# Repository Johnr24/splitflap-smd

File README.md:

# splitflap-smd
modifications of scottbez's sensor PCB design to work and fit within david kingsmans design,

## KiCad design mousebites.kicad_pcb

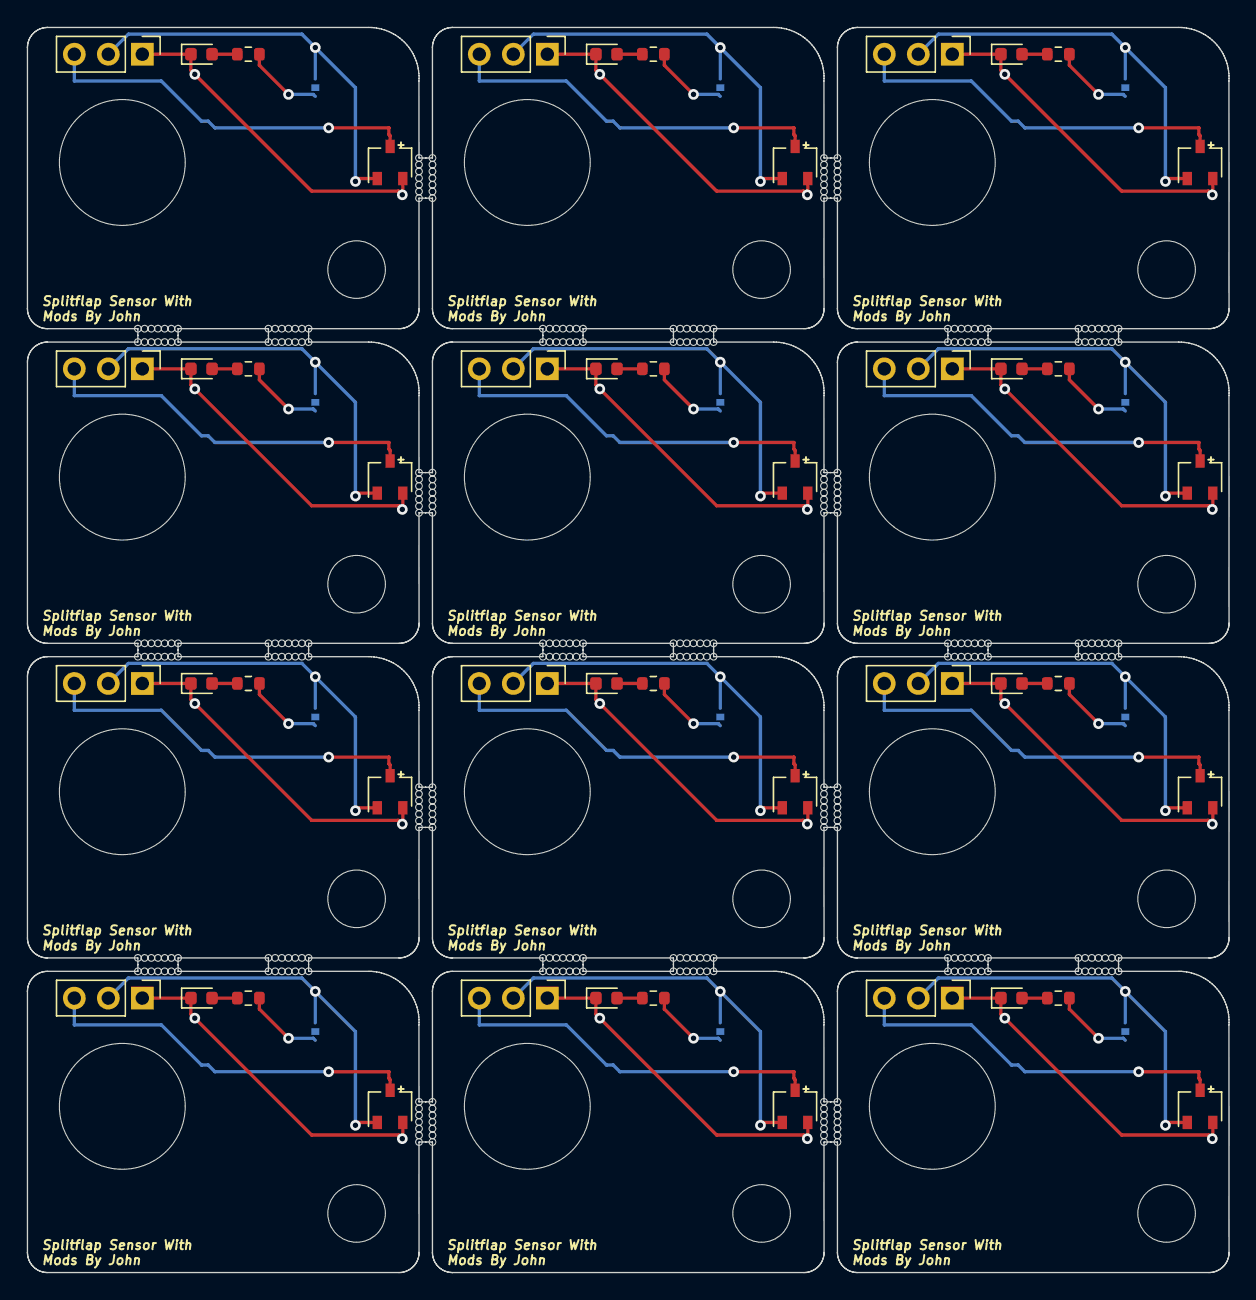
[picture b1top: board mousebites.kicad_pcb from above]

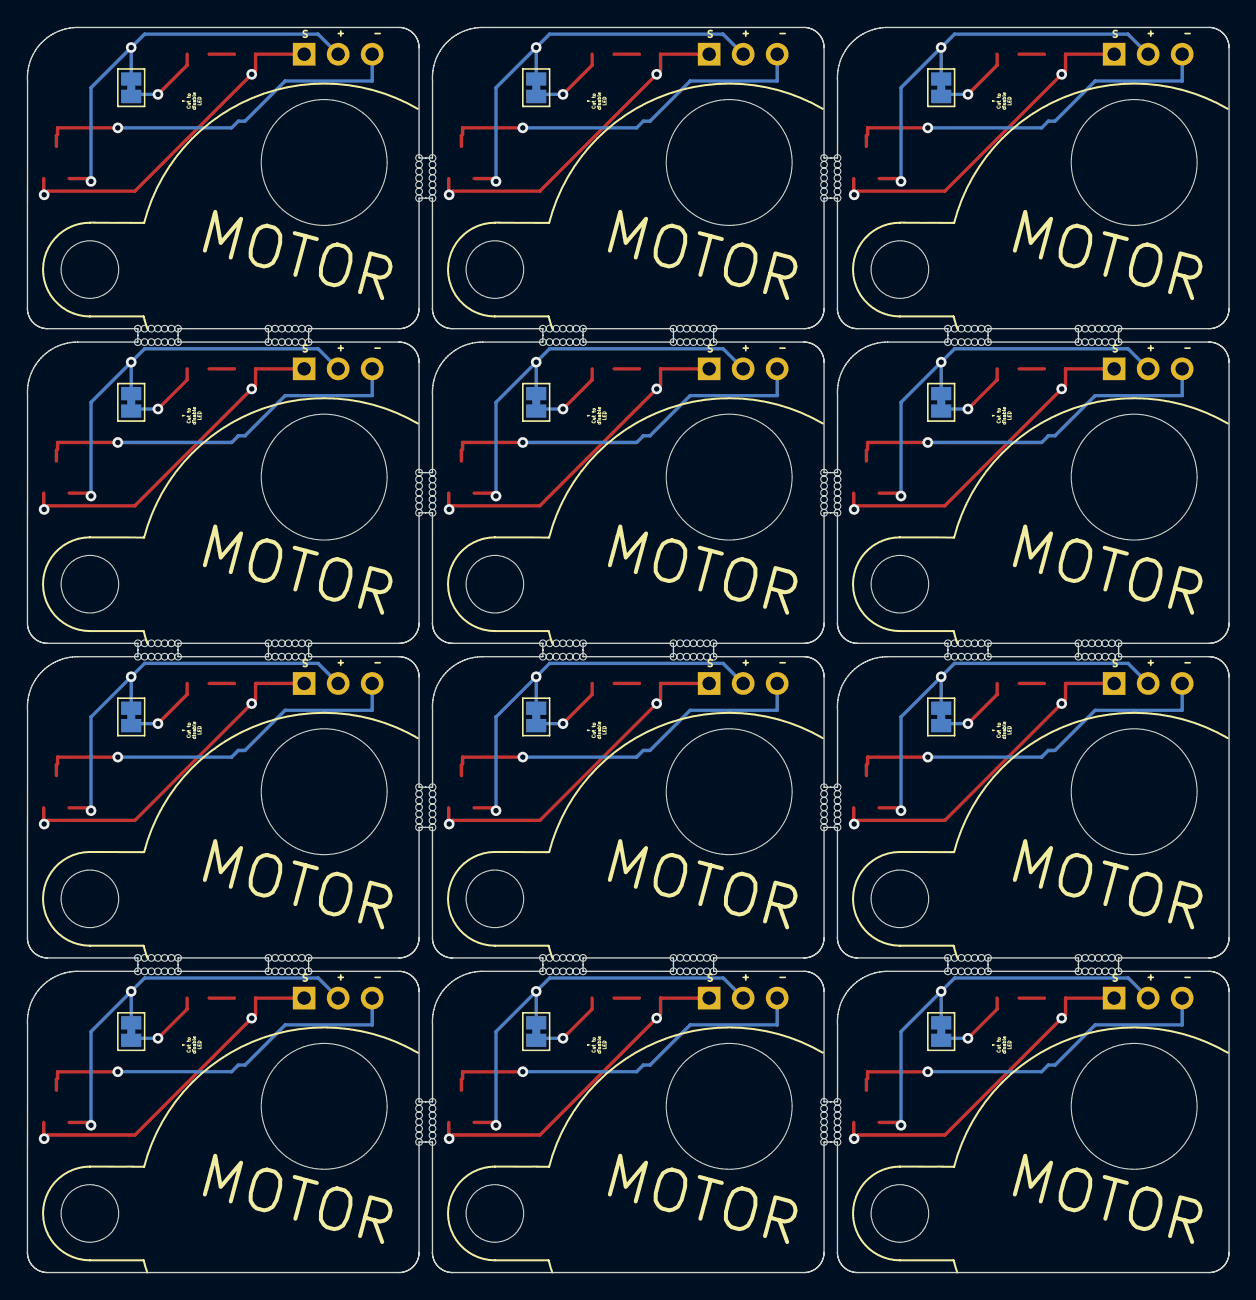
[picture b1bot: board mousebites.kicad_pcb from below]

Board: 2 copper layers, 89.8 x 93.0 mm, 448 parts (12 on the bottom side), 60 nets.

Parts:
D1, D1#2, D1#3, D1#4, D1#5, D1#6, D1#7, D1#8, D1#9, D1#10, D1#11, D1#12: LED RED; LED_0603_1608Metric
H1, H1#2, H1#3, H1#4, H1#5, H1#6, H1#7, H1#8, H1#9, H1#10, H1#11, H1#12: MountingHole; MountingHole_4.3mm_M4_ISO7380
H2, H2#2, H2#3, H2#4, H2#5, H2#6, H2#7, H2#8, H2#9, H2#10, H2#11, H2#12: MountingHole; hole_9.4
J1, J1#2, J1#3, J1#4, J1#5, J1#6, J1#7, J1#8, J1#9, J1#10, J1#11, J1#12: HEADER MALE RA; PinHeader_1x03_P2.54mm_Vertical
JP1, JP1#2, JP1#3, JP1#4, JP1#5, JP1#6, JP1#7, JP1#8, JP1#9, JP1#10, JP1#11, JP1#12: LED enable; SolderJumper-2_P1.3mm_Bridged_Pad1.0x1.5mm
KiKit_MB_1_1, KiKit_MB_1_2, KiKit_MB_1_3, KiKit_MB_1_4, KiKit_MB_1_5, KiKit_MB_1_6, KiKit_MB_1_7, KiKit_MB_2_1, KiKit_MB_2_2, KiKit_MB_2_3, KiKit_MB_2_4, KiKit_MB_2_5, KiKit_MB_2_6, KiKit_MB_2_7, KiKit_MB_3_1, KiKit_MB_3_2, KiKit_MB_3_3, KiKit_MB_3_4, KiKit_MB_3_5, KiKit_MB_3_6, KiKit_MB_3_7, KiKit_MB_4_1, KiKit_MB_4_2, KiKit_MB_4_3, KiKit_MB_4_4, KiKit_MB_4_5, KiKit_MB_4_6, KiKit_MB_4_7, KiKit_MB_5_1, KiKit_MB_5_2, KiKit_MB_5_3, KiKit_MB_5_4, KiKit_MB_5_5, KiKit_MB_5_6, KiKit_MB_5_7, KiKit_MB_6_1, KiKit_MB_6_2, KiKit_MB_6_3, KiKit_MB_6_4, KiKit_MB_6_5, KiKit_MB_6_6, KiKit_MB_6_7, KiKit_MB_7_1, KiKit_MB_7_2, KiKit_MB_7_3, KiKit_MB_7_4, KiKit_MB_7_5, KiKit_MB_7_6, KiKit_MB_7_7, KiKit_MB_8_1, KiKit_MB_8_2, KiKit_MB_8_3, KiKit_MB_8_4, KiKit_MB_8_5, KiKit_MB_8_6, KiKit_MB_8_7, KiKit_MB_9_1, KiKit_MB_9_2, KiKit_MB_9_3, KiKit_MB_9_4, KiKit_MB_9_5, KiKit_MB_9_6, KiKit_MB_9_7, KiKit_MB_10_1, KiKit_MB_10_2, KiKit_MB_10_3, KiKit_MB_10_4, KiKit_MB_10_5, KiKit_MB_10_6, KiKit_MB_10_7, KiKit_MB_11_1, KiKit_MB_11_2, KiKit_MB_11_3, KiKit_MB_11_4, KiKit_MB_11_5, KiKit_MB_11_6, KiKit_MB_11_7, KiKit_MB_12_1, KiKit_MB_12_2, KiKit_MB_12_3, KiKit_MB_12_4, KiKit_MB_12_5, KiKit_MB_12_6, KiKit_MB_12_7, KiKit_MB_13_1, KiKit_MB_13_2, KiKit_MB_13_3, KiKit_MB_13_4, KiKit_MB_13_5, KiKit_MB_13_6, KiKit_MB_13_7, KiKit_MB_14_1, KiKit_MB_14_2, KiKit_MB_14_3, KiKit_MB_14_4, KiKit_MB_14_5, KiKit_MB_14_6, KiKit_MB_14_7, KiKit_MB_15_1, KiKit_MB_15_2, KiKit_MB_15_3, KiKit_MB_15_4, KiKit_MB_15_5, KiKit_MB_15_6, KiKit_MB_15_7, KiKit_MB_16_1, KiKit_MB_16_2, KiKit_MB_16_3, KiKit_MB_16_4, KiKit_MB_16_5, KiKit_MB_16_6, KiKit_MB_16_7, KiKit_MB_17_1, KiKit_MB_17_2, KiKit_MB_17_3, KiKit_MB_17_4, KiKit_MB_17_5, KiKit_MB_17_6, KiKit_MB_17_7, KiKit_MB_18_1, KiKit_MB_18_2, KiKit_MB_18_3, KiKit_MB_18_4, KiKit_MB_18_5, KiKit_MB_18_6, KiKit_MB_18_7, KiKit_MB_19_1, KiKit_MB_19_2, KiKit_MB_19_3, KiKit_MB_19_4, KiKit_MB_19_5, KiKit_MB_19_6, KiKit_MB_19_7, KiKit_MB_20_1, KiKit_MB_20_2, KiKit_MB_20_3, KiKit_MB_20_4, KiKit_MB_20_5, KiKit_MB_20_6, KiKit_MB_20_7, KiKit_MB_21_1, KiKit_MB_21_2, KiKit_MB_21_3, KiKit_MB_21_4, KiKit_MB_21_5, KiKit_MB_21_6, KiKit_MB_21_7, KiKit_MB_22_1, KiKit_MB_22_2, KiKit_MB_22_3, KiKit_MB_22_4, KiKit_MB_22_5, KiKit_MB_22_6, KiKit_MB_22_7, KiKit_MB_23_1, KiKit_MB_23_2, KiKit_MB_23_3, KiKit_MB_23_4, KiKit_MB_23_5, KiKit_MB_23_6, KiKit_MB_23_7, KiKit_MB_24_1, KiKit_MB_24_2, KiKit_MB_24_3, KiKit_MB_24_4, KiKit_MB_24_5, KiKit_MB_24_6, KiKit_MB_24_7, KiKit_MB_25_1, KiKit_MB_25_2, KiKit_MB_25_3, KiKit_MB_25_4, KiKit_MB_25_5, KiKit_MB_25_6, KiKit_MB_25_7, KiKit_MB_26_1, KiKit_MB_26_2, KiKit_MB_26_3, KiKit_MB_26_4, KiKit_MB_26_5, KiKit_MB_26_6, KiKit_MB_26_7, KiKit_MB_27_1, KiKit_MB_27_2, KiKit_MB_27_3, KiKit_MB_27_4, KiKit_MB_27_5, KiKit_MB_27_6, KiKit_MB_27_7, KiKit_MB_28_1, KiKit_MB_28_2, KiKit_MB_28_3, KiKit_MB_28_4, KiKit_MB_28_5, KiKit_MB_28_6, KiKit_MB_28_7, KiKit_MB_29_1, KiKit_MB_29_2, KiKit_MB_29_3, KiKit_MB_29_4, KiKit_MB_29_5, KiKit_MB_29_6, KiKit_MB_29_7, KiKit_MB_30_1, KiKit_MB_30_2, KiKit_MB_30_3, KiKit_MB_30_4, KiKit_MB_30_5, KiKit_MB_30_6, KiKit_MB_30_7, KiKit_MB_31_1, KiKit_MB_31_2, KiKit_MB_31_3, KiKit_MB_31_4, KiKit_MB_31_5, KiKit_MB_31_6, KiKit_MB_31_7, KiKit_MB_32_1, KiKit_MB_32_2, KiKit_MB_32_3, KiKit_MB_32_4, KiKit_MB_32_5, KiKit_MB_32_6, KiKit_MB_32_7, KiKit_MB_33_1, KiKit_MB_33_2, KiKit_MB_33_3, KiKit_MB_33_4, KiKit_MB_33_5, KiKit_MB_33_6, KiKit_MB_33_7, KiKit_MB_34_1, KiKit_MB_34_2, KiKit_MB_34_3, KiKit_MB_34_4, KiKit_MB_34_5, KiKit_MB_34_6, KiKit_MB_34_7, KiKit_MB_35_1, KiKit_MB_35_2, KiKit_MB_35_3, KiKit_MB_35_4, KiKit_MB_35_5, KiKit_MB_35_6, KiKit_MB_35_7, KiKit_MB_36_1, KiKit_MB_36_2, KiKit_MB_36_3, KiKit_MB_36_4, KiKit_MB_36_5, KiKit_MB_36_6, KiKit_MB_36_7, KiKit_MB_37_1, KiKit_MB_37_2, KiKit_MB_37_3, KiKit_MB_37_4, KiKit_MB_37_5, KiKit_MB_37_6, KiKit_MB_37_7, KiKit_MB_38_1, KiKit_MB_38_2, KiKit_MB_38_3, KiKit_MB_38_4, KiKit_MB_38_5, KiKit_MB_38_6, KiKit_MB_38_7, KiKit_MB_39_1, KiKit_MB_39_2, KiKit_MB_39_3, KiKit_MB_39_4, KiKit_MB_39_5, KiKit_MB_39_6, KiKit_MB_39_7, KiKit_MB_40_1, KiKit_MB_40_2, KiKit_MB_40_3, KiKit_MB_40_4, KiKit_MB_40_5, KiKit_MB_40_6, KiKit_MB_40_7, KiKit_MB_41_1, KiKit_MB_41_2, KiKit_MB_41_3, KiKit_MB_41_4, KiKit_MB_41_5, KiKit_MB_41_6, KiKit_MB_41_7, KiKit_MB_42_1, KiKit_MB_42_2, KiKit_MB_42_3, KiKit_MB_42_4, KiKit_MB_42_5, KiKit_MB_42_6, KiKit_MB_42_7, KiKit_MB_43_1, KiKit_MB_43_2, KiKit_MB_43_3, KiKit_MB_43_4, KiKit_MB_43_5, KiKit_MB_43_6, KiKit_MB_43_7, KiKit_MB_44_1, KiKit_MB_44_2, KiKit_MB_44_3, KiKit_MB_44_4, KiKit_MB_44_5, KiKit_MB_44_6, KiKit_MB_44_7, KiKit_MB_45_1, KiKit_MB_45_2, KiKit_MB_45_3, KiKit_MB_45_4, KiKit_MB_45_5, KiKit_MB_45_6, KiKit_MB_45_7, KiKit_MB_46_1, KiKit_MB_46_2, KiKit_MB_46_3, KiKit_MB_46_4, KiKit_MB_46_5, KiKit_MB_46_6, KiKit_MB_46_7, KiKit_MB_47_1, KiKit_MB_47_2, KiKit_MB_47_3, KiKit_MB_47_4, KiKit_MB_47_5, KiKit_MB_47_6, KiKit_MB_47_7, KiKit_MB_48_1, KiKit_MB_48_2, KiKit_MB_48_3, KiKit_MB_48_4, KiKit_MB_48_5, KiKit_MB_48_6, KiKit_MB_48_7, KiKit_MB_49_1, KiKit_MB_49_2, KiKit_MB_49_3, KiKit_MB_49_4, KiKit_MB_49_5, KiKit_MB_49_6, KiKit_MB_49_7, KiKit_MB_50_1, KiKit_MB_50_2, KiKit_MB_50_3, KiKit_MB_50_4, KiKit_MB_50_5, KiKit_MB_50_6, KiKit_MB_50_7, KiKit_MB_51_1, KiKit_MB_51_2, KiKit_MB_51_3, KiKit_MB_51_4, KiKit_MB_51_5, KiKit_MB_51_6, KiKit_MB_51_7, KiKit_MB_52_1, KiKit_MB_52_2, KiKit_MB_52_3, KiKit_MB_52_4, KiKit_MB_52_5, KiKit_MB_52_6, KiKit_MB_52_7: NPTH
R1, R1#2, R1#3, R1#4, R1#5, R1#6, R1#7, R1#8, R1#9, R1#10, R1#11, R1#12: 1k; R_0603_1608Metric
U1, U1#2, U1#3, U1#4, U1#5, U1#6, U1#7, U1#8, U1#9, U1#10, U1#11, U1#12: HX6286; SOT-23W

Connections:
Board_0-/SIGNAL: D1#5.1 (K), J1.1, U1#2.2 (VOUT)
Board_0-GND: J1.3, U1#2.3 (GND)
Board_0-Net-(D1-A): D1#5.2 (A), R1#4.1
Board_0-Net-(JP1-B): JP1#4.2 (B), R1#4.2
Board_0-VDD: J1.2, JP1#4.1 (A), U1#2.1 (VCC)
Board_1-/SIGNAL: D1#7.1 (K), J1#6.1, U1#4.2 (VOUT)
Board_1-GND: J1#6.3, U1#4.3 (GND)
Board_1-Net-(D1-A): D1#7.2 (A), R1#11.1
Board_1-Net-(JP1-B): JP1#5.2 (B), R1#11.2
Board_1-VDD: J1#6.2, JP1#5.1 (A), U1#4.1 (VCC)
Board_2-/SIGNAL: D1#2.1 (K), J1#3.1, U1#6.2 (VOUT)
Board_2-GND: J1#3.3, U1#6.3 (GND)
Board_2-Net-(D1-A): D1#2.2 (A), R1#6.1
Board_2-Net-(JP1-B): JP1#2.2 (B), R1#6.2
Board_2-VDD: J1#3.2, JP1#2.1 (A), U1#6.1 (VCC)
Board_3-/SIGNAL: D1#12.1 (K), J1#9.1, U1#5.2 (VOUT)
Board_3-GND: J1#9.3, U1#5.3 (GND)
Board_3-Net-(D1-A): D1#12.2 (A), R1.1
Board_3-Net-(JP1-B): JP1#10.2 (B), R1.2
Board_3-VDD: J1#9.2, JP1#10.1 (A), U1#5.1 (VCC)
Board_4-/SIGNAL: D1#3.1 (K), J1#11.1, U1#12.2 (VOUT)
Board_4-GND: J1#11.3, U1#12.3 (GND)
Board_4-Net-(D1-A): D1#3.2 (A), R1#5.1
Board_4-Net-(JP1-B): JP1#12.2 (B), R1#5.2
Board_4-VDD: J1#11.2, JP1#12.1 (A), U1#12.1 (VCC)
Board_5-/SIGNAL: D1#4.1 (K), J1#10.1, U1#3.2 (VOUT)
Board_5-GND: J1#10.3, U1#3.3 (GND)
Board_5-Net-(D1-A): D1#4.2 (A), R1#2.1
Board_5-Net-(JP1-B): JP1#9.2 (B), R1#2.2
Board_5-VDD: J1#10.2, JP1#9.1 (A), U1#3.1 (VCC)
Board_6-/SIGNAL: D1#10.1 (K), J1#4.1, U1#11.2 (VOUT)
Board_6-GND: J1#4.3, U1#11.3 (GND)
Board_6-Net-(D1-A): D1#10.2 (A), R1#12.1
Board_6-Net-(JP1-B): JP1#7.2 (B), R1#12.2
Board_6-VDD: J1#4.2, JP1#7.1 (A), U1#11.1 (VCC)
Board_7-/SIGNAL: D1#6.1 (K), J1#2.1, U1#7.2 (VOUT)
Board_7-GND: J1#2.3, U1#7.3 (GND)
Board_7-Net-(D1-A): D1#6.2 (A), R1#3.1
Board_7-Net-(JP1-B): JP1#6.2 (B), R1#3.2
Board_7-VDD: J1#2.2, JP1#6.1 (A), U1#7.1 (VCC)
Board_8-/SIGNAL: D1.1 (K), J1#12.1, U1.2 (VOUT)
Board_8-GND: J1#12.3, U1.3 (GND)
Board_8-Net-(D1-A): D1.2 (A), R1#10.1
Board_8-Net-(JP1-B): JP1#3.2 (B), R1#10.2
Board_8-VDD: J1#12.2, JP1#3.1 (A), U1.1 (VCC)
Board_9-/SIGNAL: D1#9.1 (K), J1#7.1, U1#9.2 (VOUT)
Board_9-GND: J1#7.3, U1#9.3 (GND)
Board_9-Net-(D1-A): D1#9.2 (A), R1#8.1
Board_9-Net-(JP1-B): JP1.2 (B), R1#8.2
Board_9-VDD: J1#7.2, JP1.1 (A), U1#9.1 (VCC)
Board_10-/SIGNAL: D1#11.1 (K), J1#5.1, U1#10.2 (VOUT)
Board_10-GND: J1#5.3, U1#10.3 (GND)
Board_10-Net-(D1-A): D1#11.2 (A), R1#9.1
Board_10-Net-(JP1-B): JP1#11.2 (B), R1#9.2
Board_10-VDD: J1#5.2, JP1#11.1 (A), U1#10.1 (VCC)
Board_11-/SIGNAL: D1#8.1 (K), J1#8.1, U1#8.2 (VOUT)
Board_11-GND: J1#8.3, U1#8.3 (GND)
Board_11-Net-(D1-A): D1#8.2 (A), R1#7.1
Board_11-Net-(JP1-B): JP1#8.2 (B), R1#7.2
Board_11-VDD: J1#8.2, JP1#8.1 (A), U1#8.1 (VCC)

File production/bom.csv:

Designator,Footprint,Quantity,Value,LCSC Part #
"D1_12, D1_11, D1_10, D1_9, D1_8, D1_7, D1_6, D1_5, D1_4, D1_3, D1_2, D1",0603,12,LED RED,C2286
"J1_12, J1_11, J1_10, J1_9, J1_8, J1_7, J1_6, J1_5, J1_4, J1_3, J1_2, J1",PinHeader_1x03_P2.54mm_Vertical,12,HEADER MALE RA,
"KiKit_MB_10_1, KiKit_MB_10_2, KiKit_MB_10_3, KiKit_MB_10_4, KiKit_MB_10_5, KiKit_MB_10_6, KiKit_MB_10_7, KiKit_MB_11_1, KiKit_MB_11_2, KiKit_MB_11_3, KiKit_MB_11_4, KiKit_MB_11_5, KiKit_MB_11_6, KiKit_MB_11_7, KiKit_MB_12_1, KiKit_MB_12_2, KiKit_MB_12_3, KiKit_MB_12_4, KiKit_MB_12_5, KiKit_MB_12_6, KiKit_MB_12_7, KiKit_MB_13_1, KiKit_MB_13_2, KiKit_MB_13_3, KiKit_MB_13_4, KiKit_MB_13_5, KiKit_MB_13_6, KiKit_MB_13_7, KiKit_MB_14_1, KiKit_MB_14_2, KiKit_MB_14_3, KiKit_MB_14_4, KiKit_MB_14_5, KiKit_MB_14_6, KiKit_MB_14_7, KiKit_MB_15_1, KiKit_MB_15_2, KiKit_MB_15_3, KiKit_MB_15_4, KiKit_MB_15_5, KiKit_MB_15_6, KiKit_MB_15_7, KiKit_MB_16_1, KiKit_MB_16_2, KiKit_MB_16_3, KiKit_MB_16_4, KiKit_MB_16_5, KiKit_MB_16_6, KiKit_MB_16_7, KiKit_MB_17_1, KiKit_MB_17_2, KiKit_MB_17_3, KiKit_MB_17_4, KiKit_MB_17_5, KiKit_MB_17_6, KiKit_MB_17_7, KiKit_MB_18_1, KiKit_MB_18_2, KiKit_MB_18_3, KiKit_MB_18_4, KiKit_MB_18_5, KiKit_MB_18_6, KiKit_MB_18_7, KiKit_MB_19_1, KiKit_MB_19_2, KiKit_MB_19_3, KiKit_MB_19_4, KiKit_MB_19_5, KiKit_MB_19_6, KiKit_MB_19_7, KiKit_MB_1_1, KiKit_MB_1_2, KiKit_MB_1_3, KiKit_MB_1_4, KiKit_MB_1_5, KiKit_MB_1_6, KiKit_MB_1_7, KiKit_MB_20_1, KiKit_MB_20_2, KiKit_MB_20_3, KiKit_MB_20_4, KiKit_MB_20_5, KiKit_MB_20_6, KiKit_MB_20_7, KiKit_MB_21_1, KiKit_MB_21_2, KiKit_MB_21_3, KiKit_MB_21_4, KiKit_MB_21_5, KiKit_MB_21_6, KiKit_MB_21_7, KiKit_MB_22_1, KiKit_MB_22_2, KiKit_MB_22_3, KiKit_MB_22_4, KiKit_MB_22_5, KiKit_MB_22_6, KiKit_MB_22_7, KiKit_MB_23_1, KiKit_MB_23_2, KiKit_MB_23_3, KiKit_MB_23_4, KiKit_MB_23_5, KiKit_MB_23_6, KiKit_MB_23_7, KiKit_MB_24_1, KiKit_MB_24_2, KiKit_MB_24_3, KiKit_MB_24_4, KiKit_MB_24_5, KiKit_MB_24_6, KiKit_MB_24_7, KiKit_MB_25_1, KiKit_MB_25_2, KiKit_MB_25_3, KiKit_MB_25_4, KiKit_MB_25_5, KiKit_MB_25_6, KiKit_MB_25_7, KiKit_MB_26_1, KiKit_MB_26_2, KiKit_MB_26_3, KiKit_MB_26_4, KiKit_MB_26_5, KiKit_MB_26_6, KiKit_MB_26_7, KiKit_MB_27_1, KiKit_MB_27_2, KiKit_MB_27_3, KiKit_MB_27_4, KiKit_MB_27_5, KiKit_MB_27_6, KiKit_MB_27_7, KiKit_MB_28_1, KiKit_MB_28_2, KiKit_MB_28_3, KiKit_MB_28_4, KiKit_MB_28_5, KiKit_MB_28_6, KiKit_MB_28_7, KiKit_MB_29_1, KiKit_MB_29_2, KiKit_MB_29_3, KiKit_MB_29_4, KiKit_MB_29_5, KiKit_MB_29_6, KiKit_MB_29_7, KiKit_MB_2_1, KiKit_MB_2_2, KiKit_MB_2_3, KiKit_MB_2_4, KiKit_MB_2_5, KiKit_MB_2_6, KiKit_MB_2_7, KiKit_MB_30_1, KiKit_MB_30_2, KiKit_MB_30_3, KiKit_MB_30_4, KiKit_MB_30_5, KiKit_MB_30_6, KiKit_MB_30_7, KiKit_MB_31_1, KiKit_MB_31_2, KiKit_MB_31_3, KiKit_MB_31_4, KiKit_MB_31_5, KiKit_MB_31_6, KiKit_MB_31_7, KiKit_MB_32_1, KiKit_MB_32_2, KiKit_MB_32_3, KiKit_MB_32_4, KiKit_MB_32_5, KiKit_MB_32_6, KiKit_MB_32_7, KiKit_MB_33_1, KiKit_MB_33_2, KiKit_MB_33_3, KiKit_MB_33_4, KiKit_MB_33_5, KiKit_MB_33_6, KiKit_MB_33_7, KiKit_MB_34_1, KiKit_MB_34_2, KiKit_MB_34_3, KiKit_MB_34_4, KiKit_MB_34_5, KiKit_MB_34_6, KiKit_MB_34_7, KiKit_MB_35_1, KiKit_MB_35_2, KiKit_MB_35_3, KiKit_MB_35_4, KiKit_MB_35_5, KiKit_MB_35_6, KiKit_MB_35_7, KiKit_MB_36_1, KiKit_MB_36_2, KiKit_MB_36_3, KiKit_MB_36_4",NPTH,200,NPTH,
"KiKit_MB_36_5, KiKit_MB_36_6, KiKit_MB_36_7, KiKit_MB_37_1, KiKit_MB_37_2, KiKit_MB_37_3, KiKit_MB_37_4, KiKit_MB_37_5, KiKit_MB_37_6, KiKit_MB_37_7, KiKit_MB_38_1, KiKit_MB_38_2, KiKit_MB_38_3, KiKit_MB_38_4, KiKit_MB_38_5, KiKit_MB_38_6, KiKit_MB_38_7, KiKit_MB_39_1, KiKit_MB_39_2, KiKit_MB_39_3, KiKit_MB_39_4, KiKit_MB_39_5, KiKit_MB_39_6, KiKit_MB_39_7, KiKit_MB_3_1, KiKit_MB_3_2, KiKit_MB_3_3, KiKit_MB_3_4, KiKit_MB_3_5, KiKit_MB_3_6, KiKit_MB_3_7, KiKit_MB_40_1, KiKit_MB_40_2, KiKit_MB_40_3, KiKit_MB_40_4, KiKit_MB_40_5, KiKit_MB_40_6, KiKit_MB_40_7, KiKit_MB_41_1, KiKit_MB_41_2, KiKit_MB_41_3, KiKit_MB_41_4, KiKit_MB_41_5, KiKit_MB_41_6, KiKit_MB_41_7, KiKit_MB_42_1, KiKit_MB_42_2, KiKit_MB_42_3, KiKit_MB_42_4, KiKit_MB_42_5, KiKit_MB_42_6, KiKit_MB_42_7, KiKit_MB_43_1, KiKit_MB_43_2, KiKit_MB_43_3, KiKit_MB_43_4, KiKit_MB_43_5, KiKit_MB_43_6, KiKit_MB_43_7, KiKit_MB_44_1, KiKit_MB_44_2, KiKit_MB_44_3, KiKit_MB_44_4, KiKit_MB_44_5, KiKit_MB_44_6, KiKit_MB_44_7, KiKit_MB_45_1, KiKit_MB_45_2, KiKit_MB_45_3, KiKit_MB_45_4, KiKit_MB_45_5, KiKit_MB_45_6, KiKit_MB_45_7, KiKit_MB_46_1, KiKit_MB_46_2, KiKit_MB_46_3, KiKit_MB_46_4, KiKit_MB_46_5, KiKit_MB_46_6, KiKit_MB_46_7, KiKit_MB_47_1, KiKit_MB_47_2, KiKit_MB_47_3, KiKit_MB_47_4, KiKit_MB_47_5, KiKit_MB_47_6, KiKit_MB_47_7, KiKit_MB_48_1, KiKit_MB_48_2, KiKit_MB_48_3, KiKit_MB_48_4, KiKit_MB_48_5, KiKit_MB_48_6, KiKit_MB_48_7, KiKit_MB_49_1, KiKit_MB_49_2, KiKit_MB_49_3, KiKit_MB_49_4, KiKit_MB_49_5, KiKit_MB_49_6, KiKit_MB_49_7, KiKit_MB_4_1, KiKit_MB_4_2, KiKit_MB_4_3, KiKit_MB_4_4, KiKit_MB_4_5, KiKit_MB_4_6, KiKit_MB_4_7, KiKit_MB_50_1, KiKit_MB_50_2, KiKit_MB_50_3, KiKit_MB_50_4, KiKit_MB_50_5, KiKit_MB_50_6, KiKit_MB_50_7, KiKit_MB_51_1, KiKit_MB_51_2, KiKit_MB_51_3, KiKit_MB_51_4, KiKit_MB_51_5, KiKit_MB_51_6, KiKit_MB_51_7, KiKit_MB_52_1, KiKit_MB_52_2, KiKit_MB_52_3, KiKit_MB_52_4, KiKit_MB_52_5, KiKit_MB_52_6, KiKit_MB_52_7, KiKit_MB_5_1, KiKit_MB_5_2, KiKit_MB_5_3, KiKit_MB_5_4, KiKit_MB_5_5, KiKit_MB_5_6, KiKit_MB_5_7, KiKit_MB_6_1, KiKit_MB_6_2, KiKit_MB_6_3, KiKit_MB_6_4, KiKit_MB_6_5, KiKit_MB_6_6, KiKit_MB_6_7, KiKit_MB_7_1, KiKit_MB_7_2, KiKit_MB_7_3, KiKit_MB_7_4, KiKit_MB_7_5, KiKit_MB_7_6, KiKit_MB_7_7, KiKit_MB_8_1, KiKit_MB_8_2, KiKit_MB_8_3, KiKit_MB_8_4, KiKit_MB_8_5, KiKit_MB_8_6, KiKit_MB_8_7, KiKit_MB_9_1, KiKit_MB_9_2, KiKit_MB_9_3, KiKit_MB_9_4, KiKit_MB_9_5, KiKit_MB_9_6, KiKit_MB_9_7",NPTH,164,NPTH,
"R1_12, R1_11, R1_10, R1_9, R1_8, R1_7, R1_6, R1_5, R1_4, R1_3, R1_2, R1",0603,12,1k,C21190
"U1_12, U1_11, U1_10, U1_9, U1_8, U1_7, U1_6, U1_5, U1_4, U1_3, U1_2, U1",SOT-23W,12,HX6286,C495736

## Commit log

2024-09-20 Create Licence
